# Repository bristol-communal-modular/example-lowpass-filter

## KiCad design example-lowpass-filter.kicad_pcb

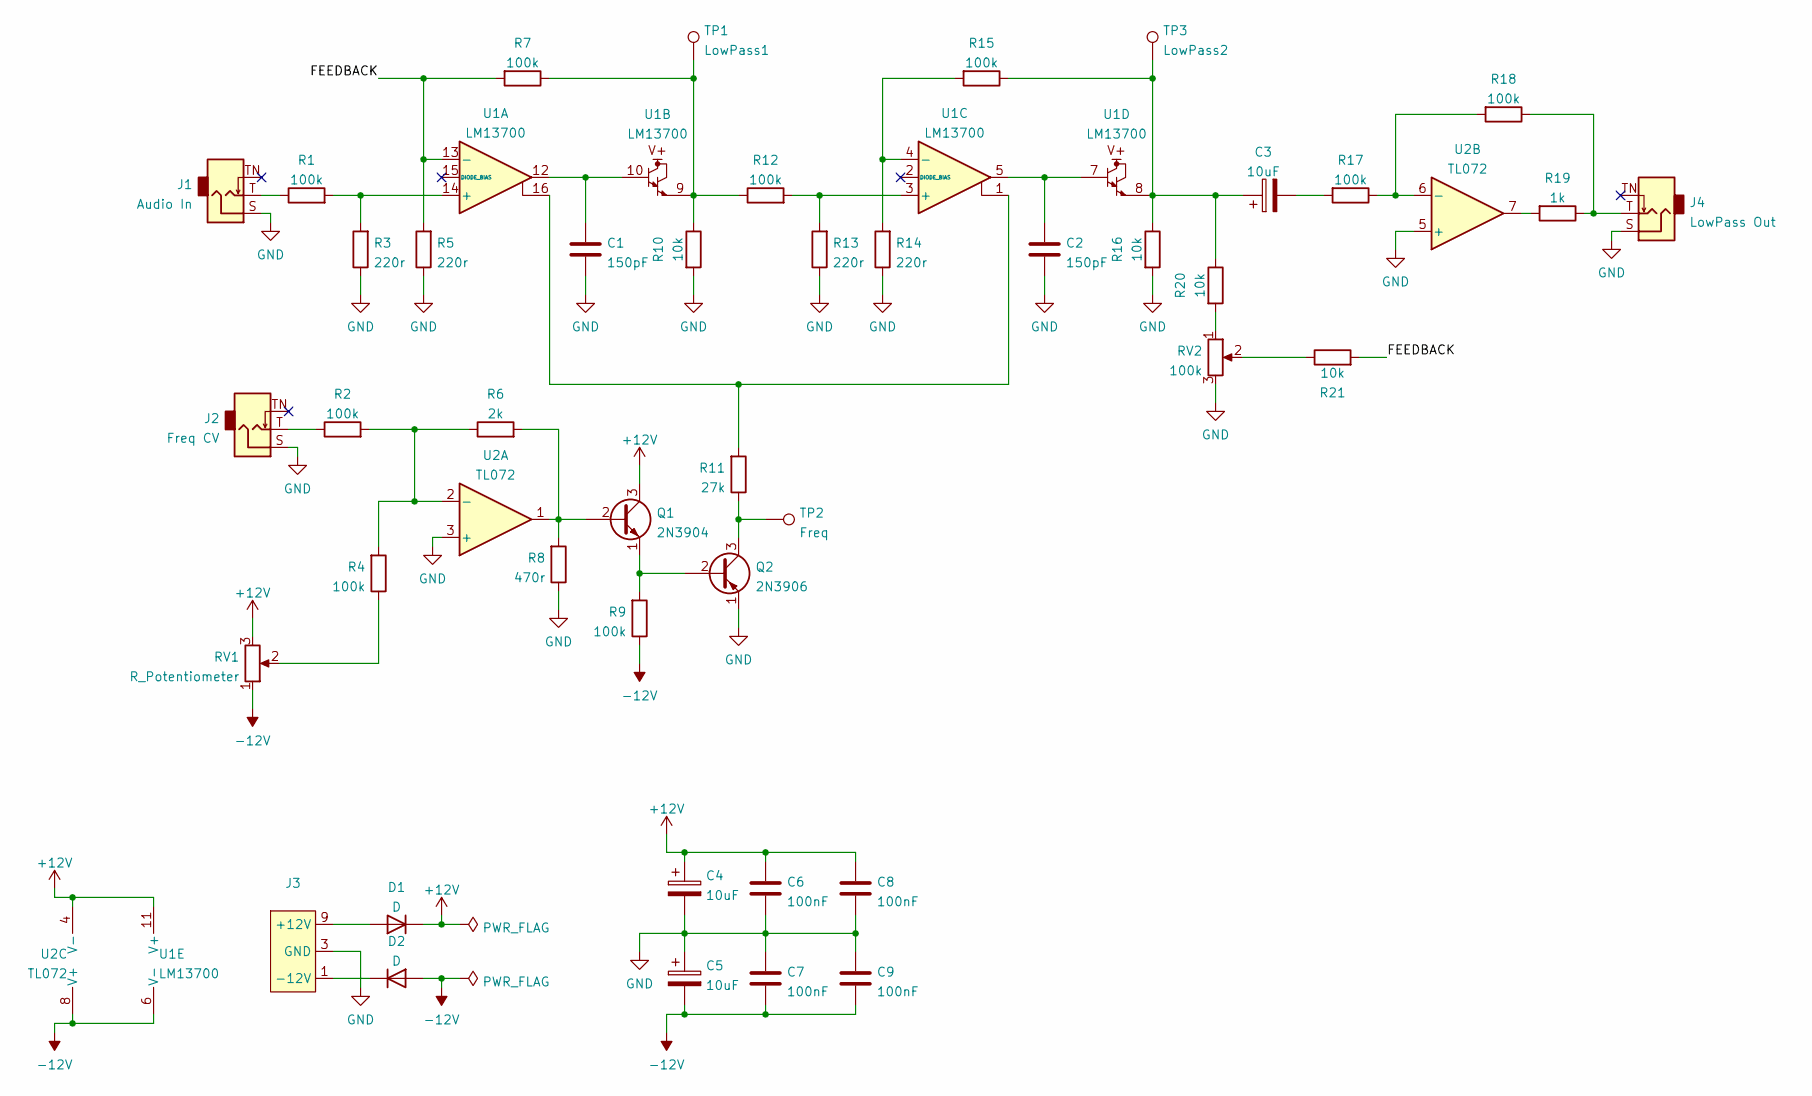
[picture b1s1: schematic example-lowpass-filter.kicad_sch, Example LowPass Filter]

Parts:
C1, C2: 150pF; C_Rect_L7.0mm_W3.5mm_P5.00mm
C3, C4, C5: 10uF; CP_Radial_D5.0mm_P2.00mm
C6, C7, C8, C9: 100nF; C_Rect_L7.0mm_W3.5mm_P5.00mm
D1, D2: D; Diode_THT_P10.16mm_Horizontal
J1: Audio In; Jack_3.5mm_QingPu_WQP-PJ398SM_Vertical
J2: Freq CV; Jack_3.5mm_QingPu_WQP-PJ398SM_Vertical
J3: Eurorack_Power_Small; Eurorack_PowerHeader_2x05_P2.54mm_Bare
J4: LowPass Out; Jack_3.5mm_QingPu_WQP-PJ398SM_Vertical
Q1: 2N3904; TO-92_Inline_Wide
Q2: 2N3906; TO-92_Inline_Wide
R1, R2, R4, R7, R9, R12, R15, R17, R18: 100k; Resistor_THT_L6.3mm_D2.5mm_P10.16mm_Horizontal
R3, R5, R13, R14: 220r; Resistor_THT_L6.3mm_D2.5mm_P10.16mm_Horizontal
R6: 2k; Resistor_THT_L6.3mm_D2.5mm_P10.16mm_Horizontal
R8: 470r; Resistor_THT_L6.3mm_D2.5mm_P10.16mm_Horizontal
R10, R16, R20, R21: 10k; Resistor_THT_L6.3mm_D2.5mm_P10.16mm_Horizontal
R11: 27k; Resistor_THT_L6.3mm_D2.5mm_P10.16mm_Horizontal
R19: 1k; Resistor_THT_L6.3mm_D2.5mm_P10.16mm_Horizontal
RV1: R_Potentiometer; Potentiometer_Alpha_RD901F-40-00D_Single_Vertical
RV2: 100k; Potentiometer_Alpha_RD901F-40-00D_Single_Vertical
TP1: LowPass1; TestPoint_Loop_D2.54mm_Drill1.5mm_Beaded
TP2: Freq; TestPoint_Loop_D2.54mm_Drill1.5mm_Beaded
TP3: LowPass2; TestPoint_Loop_D2.54mm_Drill1.5mm_Beaded
U1: LM13700; DIP-16_W7.62mm_Socket
U2: TL072; DIP-8_W7.62mm_Socket

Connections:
+12V: C4.1, C6.1, C8.1, D1.1 (K), Q1.3 (C), RV1.3, U1.11 (V+), U2.4 (V-)
-12V: C5.2, C7.2, C9.2, D2.2 (A), R9.1, RV1.1, U1.6 (V-), U2.8 (V+)
/FEEDBACK: R5.2, R7.2, R21.2, U1.13 (-)
GND: C1.2, C2.2, C4.2, C5.1, C6.2, C7.1, C8.2, C9.1, J1.S, J2.S, J3.3 (GND), J3.4 (GND), J3.5 (GND), J3.6 (GND), J3.7 (GND), J3.8 (GND), J4.S, Q2.1 (E), R3.1, R5.1, R8.1, R10.2, R13.1, R14.1, R16.2, RV2.3, U2.3 (+), U2.5 (+)
unnamed: C1.1, U1.10, U1.12
unnamed: C2.1, U1.5, U1.7
unnamed: D1.2 (A), J3.9 (+12V), J3.10 (+12V)
unnamed: D2.1 (K), J3.1 (-12V), J3.2 (-12V)
unnamed: J1.T, R1.1
unnamed: J2.T, R2.1
unnamed: J4.T, R18.1, R19.1
unnamed: Q1.1 (E), Q2.2 (B), R9.2
unnamed: Q1.2 (B), R6.2, R8.2, U2.1
unnamed: Q2.3 (C), R11.1, TP2.1
unnamed: R1.2, R3.2, U1.14 (+)
unnamed: R2.2, R4.2, R6.1, U2.2 (-)
unnamed: R4.1, RV1.2
unnamed: R7.1, R10.1, R12.1, TP1.1, U1.9
unnamed: R11.2, U1.1, U1.16
unnamed: R12.2, R13.2, U1.3 (+)
unnamed: R14.2, R15.2, U1.4 (-)
unnamed: C3.1, R15.1, R16.1, R20.1, TP3.1, U1.8
unnamed: R17.1, R18.2, U2.6 (-)
unnamed: C3.2, R17.2
unnamed: R19.2, U2.7
unnamed: R20.2, RV2.1
unnamed: R21.1, RV2.2

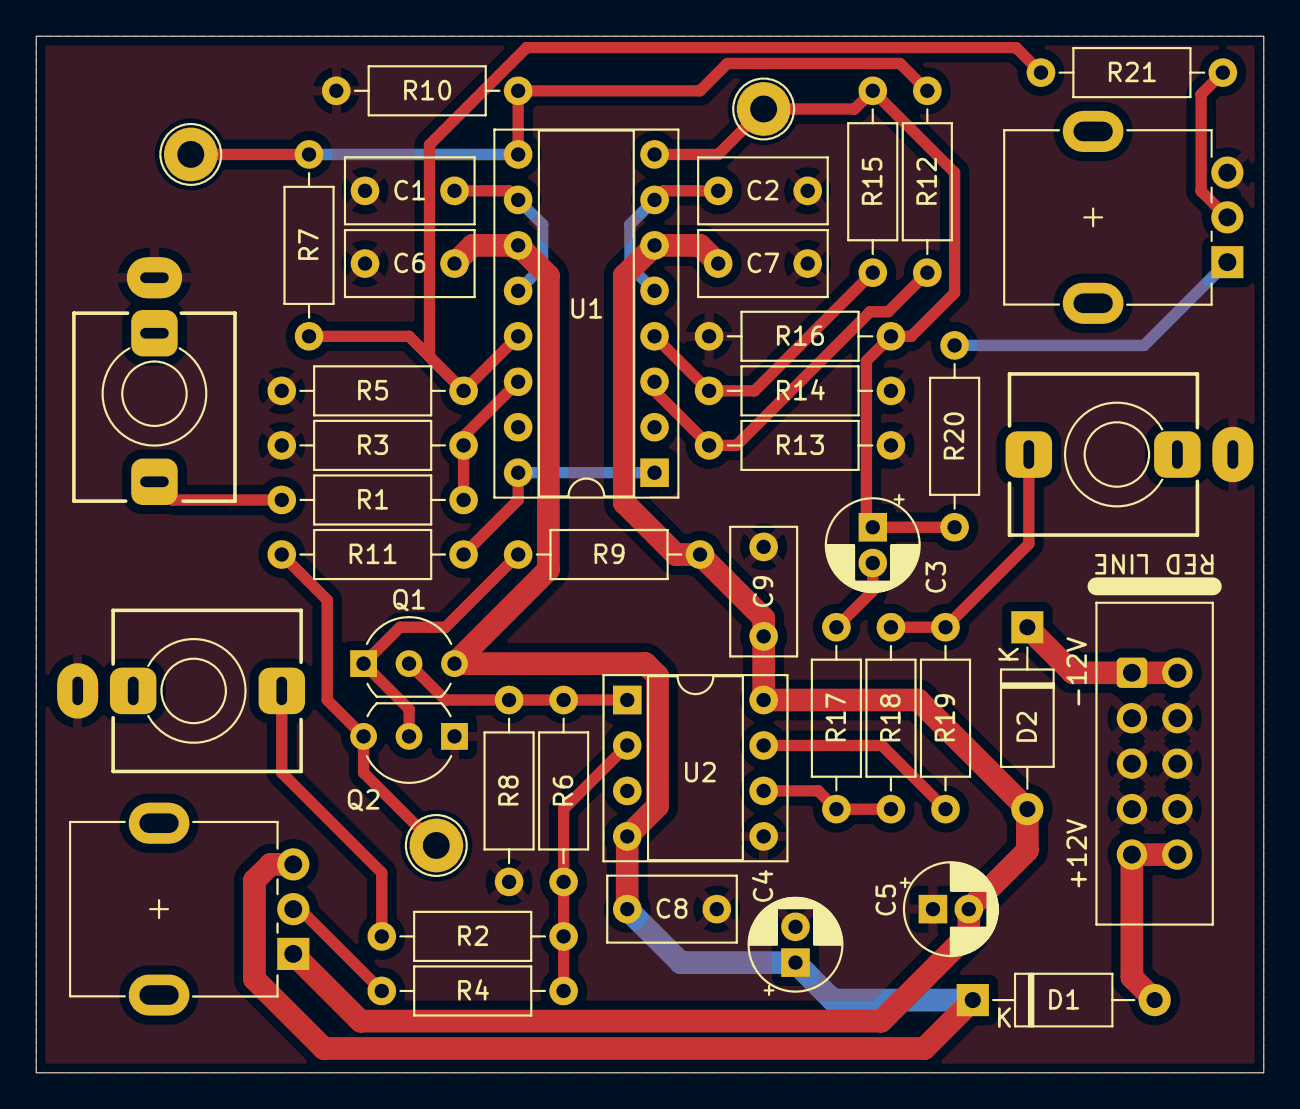
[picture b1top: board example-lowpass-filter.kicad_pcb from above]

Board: 2 copper layers, 68.6 x 57.9 mm, 45 parts (0 on the bottom side), 27 nets.
